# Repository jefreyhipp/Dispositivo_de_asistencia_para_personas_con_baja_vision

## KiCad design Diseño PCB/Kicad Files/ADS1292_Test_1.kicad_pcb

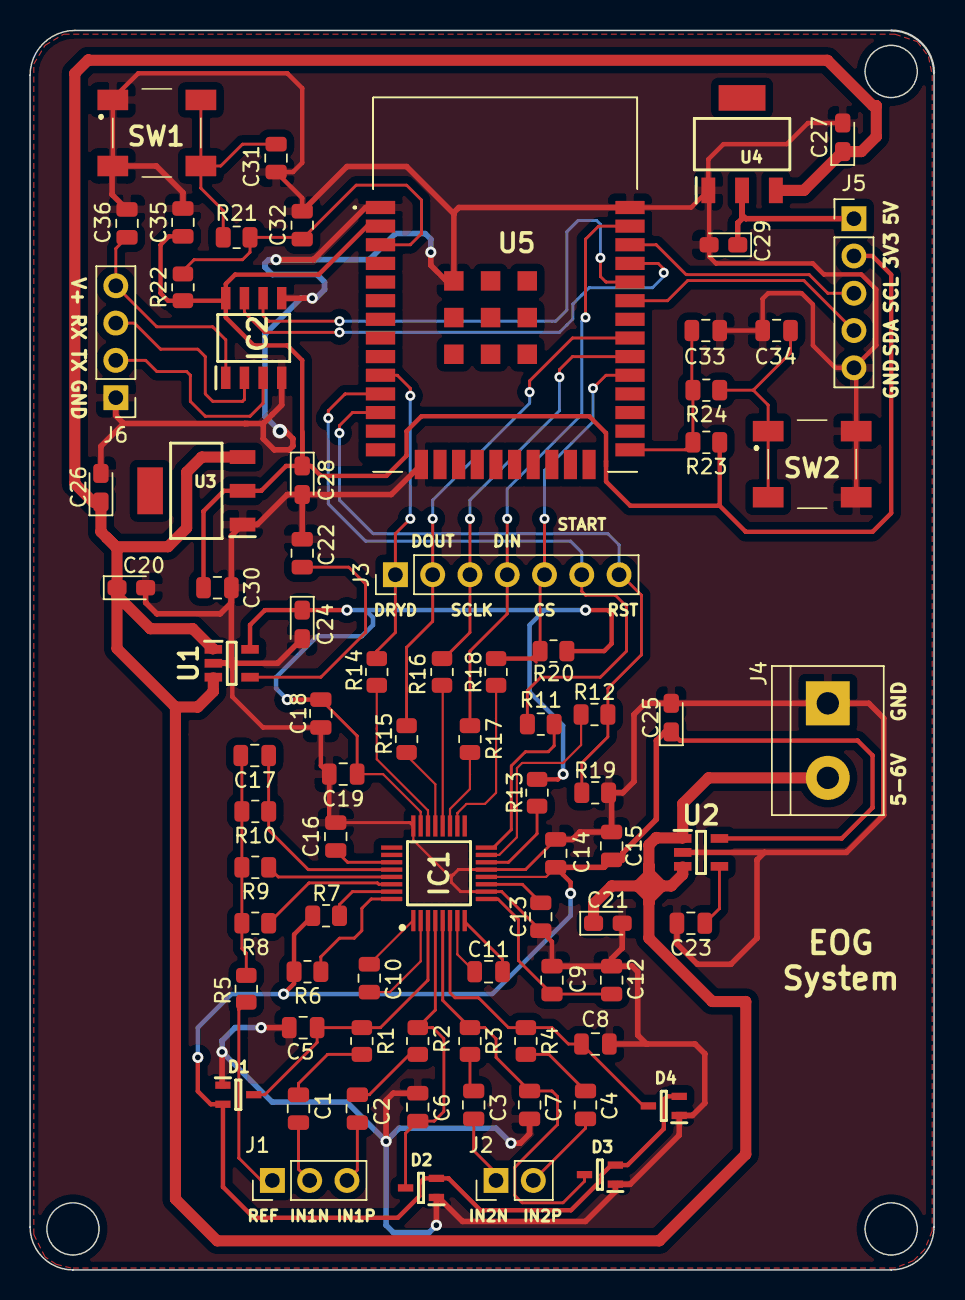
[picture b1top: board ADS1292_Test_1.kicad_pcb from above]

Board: 2 copper layers, 61.6 x 84.5 mm, 79 parts (0 on the bottom side), 60 nets.

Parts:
C1, C2, C3, C4, C13, C14, C16, C18: 1µF; C_0805_2012Metric
C5, C6, C7, C8: 1nF; C_0805_2012Metric
C9, C15, C19, C30, C31, C34, C35, C36: 100nF; C_0805_2012Metric
C10, C11: 4.7nF; C_0805_2012Metric
C12: 10µF; C_0805_2012Metric
C17: 1.5nF; C_0805_2012Metric
C20, C21, C24, C25: 1uF; CP_EIA-2012-12_Kemet-R_Pad1.30x1.05mm_HandSolder
C22, C23: 10nF; C_0805_2012Metric
C26, C27: 10uF; CP_EIA-2012-12_Kemet-R_Pad1.30x1.05mm_HandSolder
C28, C29: 22uF; CP_EIA-2012-12_Kemet-R_Pad1.30x1.05mm_HandSolder
C32, C33: 1uF; C_0805_2012Metric
D1, D2, D3, D4: BAT54SW; SOT65P210X110-3N
IC1: ADS1292IPBS; QFP50P700X700X120-32N
IC2: ISO7221BDR; SOIC127P600X175-8N
J1: Conn_01x03_Male; PinHeader_1x03_P2.54mm_Vertical
J2: Conn_01x02_Male; PinHeader_1x02_P2.54mm_Vertical
J3: Conn_01x07_Male; PinHeader_1x07_P2.54mm_Vertical
J4: Conn_01x02_Male; TerminalBlock_bornier-2_P5.08mm
J5: Conn_01x05_Male; PinHeader_1x05_P2.54mm_Vertical
J6: Conn_01x04_Male; PinHeader_1x04_P2.54mm_Vertical
R1, R2, R3, R4, R5, R9: 100kΩ; R_0805_2012Metric
R6, R7, R13, R19, R20: 10kΩ; R_0805_2012Metric
R8, R11, R12, R14, R15, R16, R17, R18, R21, R24: 0E; R_0805_2012Metric
R10: 1MΩ; R_0805_2012Metric
R22, R23: 10k; R_0805_2012Metric
SW1, SW2: SW_DPST; LL3301FF065QJ
U1, U2: TC2185-3.3VxCTTR; SOT95P280X145-5N
U3: LM1117-3.3; SOT230P700X180-4N
U4: LM1117-5.0; SOT230P700X180-4N
U5: ESP32-WROOM-32U; ESP32WROOM32EM113EH3200PH3Q0

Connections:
+3V3: C28.1, C30.1, C35.2, IC2.8, J5.2, R22.1, R23.1, U3.2, U5.2
+5V: C29.1, J5.1, U4.2
+BATT: C20.1, C21.1, C26.1, C27.1, J4.2, U1.1, U1.3, U2.1, U2.3, U3.3, U4.3
/ESP32/RX: IC2.2, J6.3
/ESP32/TX: IC2.3, J6.2
ADS_CS: J3.5, R18.1, R20.1, U5.29
ADS_DIN: J3.4, R17.1, U5.37
ADS_DOUT: J3.2, R15.1, U5.31
ADS_DRDY: J3.1, R14.1, U5.10
ADS_RESET: J3.7, R12.1, R19.1, U5.12
ADS_SCLK: J3.3, R16.1, U5.30
ADS_START: J3.6, R11.1, U5.11
GND: C5.2, C6.2, C7.2, C8.2, C9.2, C12.2, C13.1, C14.1, C15.1, C16.2, C18.2, C19.2, C20.2, C21.2, C22.2, C23.2, C24.2, C25.2, C26.2, C27.2, C28.2, C29.2, C30.2, C31.1, C32.2, C33.2, C34.1, C35.1, C36.1, D1.1, D2.1, D3.1, D4.1, IC1.10, IC1.13, IC1.24, IC2.4, IC2.5, J4.1, J5.5, J6.1, R19.2, SW1.1, SW1.3, SW2.2, SW2.4, U1.2, U2.2, U3.1, U4.1, U5.1, U5.15, U5.38, U5.39
unnamed: C1.1, R1.2
unnamed: C1.2, J1.2
unnamed: C2.1, R2.2
unnamed: C2.2, J1.3
unnamed: C3.1, R3.2
unnamed: C3.2, J2.1
unnamed: C4.1, R4.2
unnamed: C4.2, J2.2
unnamed: C5.1, D1.3, IC1.3, R1.1
unnamed: C6.1, D2.3, IC1.4, R2.1
unnamed: C7.1, D3.3, IC1.5, R3.1
unnamed: C8.1, D4.3, IC1.6, R4.1
unnamed: C10.1, IC1.1
unnamed: C10.2, IC1.2
unnamed: C11.1, IC1.7
unnamed: C11.2, IC1.8
unnamed: C9.1, C12.1, IC1.9
unnamed: C13.2, IC1.11
unnamed: C16.1, IC1.27
unnamed: C17.1, IC1.28, R10.1
unnamed: C17.2, R5.2, R8.2, R9.2, R10.2
unnamed: C22.1, U1.4
unnamed: C23.1, U2.4
unnamed: C31.2, R21.1, SW1.2, SW1.4
unnamed: C32.1, R21.2, R22.2, U5.3
unnamed: C33.1, R23.2, R24.2, U5.25
unnamed: C34.2, R24.1, SW2.1, SW2.3
unnamed: C36.2, IC2.1, J6.4
unnamed: IC1.14, R13.1
unnamed: IC1.15, R12.2
unnamed: IC1.16, R11.2
unnamed: IC1.18, R18.2
unnamed: IC1.19, R17.2
unnamed: IC1.20, R16.2
unnamed: IC1.21, R15.2
unnamed: IC1.22, R14.2
unnamed: IC1.29, R9.1
unnamed: IC1.30, R8.1
unnamed: IC1.31, R7.2
unnamed: IC1.32, R6.2
unnamed: J1.1, R5.1
SCL: J5.3, U5.36
SDA: J5.4, U5.33
U0RXD: IC2.6, U5.34
U0TXD: IC2.7, U5.35
VDD: C18.1, C19.1, C24.1, IC1.23, R13.2, R20.2, U1.5
VDDA: C14.2, C15.2, C25.1, D1.2, D2.2, D3.2, D4.2, IC1.12, R6.1, R7.1, U2.5

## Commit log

2021-05-15 version 1.0
2021-05-15 version 1.1
